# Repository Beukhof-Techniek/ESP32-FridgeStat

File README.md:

# ESP32-FridgeStat

ESP32 Refrigerator Thermostat with Signal K support
-----

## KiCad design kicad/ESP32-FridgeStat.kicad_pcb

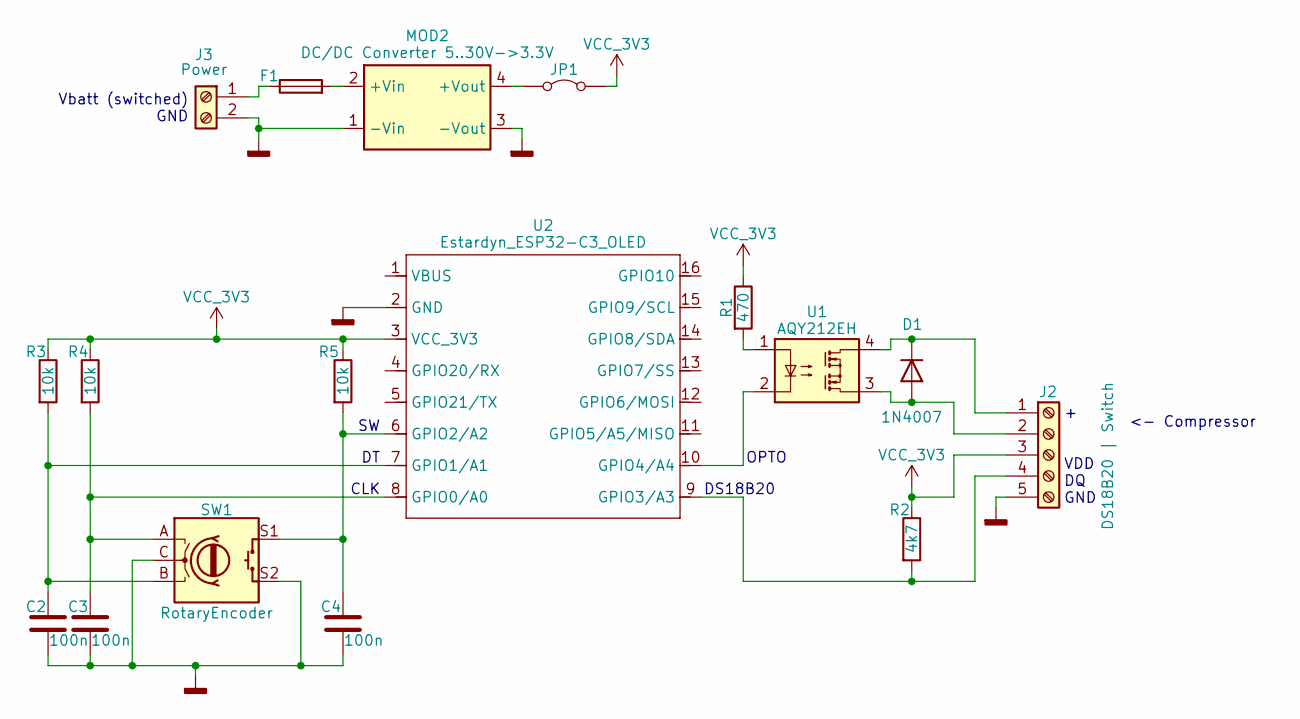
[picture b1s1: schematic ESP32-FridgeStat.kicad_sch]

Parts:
C2, C3, C4: 100n; C_Disc_D3.0mm_W1.6mm_P2.50mm
D1: 1N4007; D_DO-34_SOD68_P7.62mm_Horizontal
F1: 250mA F; Fuseholder_Littelfuse_Nano2_154x
J2: DS18B20 | Switch; TerminalBlock_MaiXu_MX126-5.0-05P_1x05_P5.00mm
J3: Power; TerminalBlock_MaiXu_MX126-5.0-02P_1x02_P5.00mm
JP1: Jumper_2_Bridged; TestPoint_2Pads_Pitch2.54mm_Drill0.8mm
MOD2: DC/DC Converter 5..30V->3.3V; DCDC_Converter_Aliexpress_4pin_17x12mm
R1: 470; R_Axial_DIN0204_L3.6mm_D1.6mm_P7.62mm_Horizontal
R2: 4k7; R_Axial_DIN0204_L3.6mm_D1.6mm_P7.62mm_Horizontal
R3, R4, R5: 10k; R_Axial_DIN0204_L3.6mm_D1.6mm_P7.62mm_Horizontal
SW1: RotaryEncoder; RotaryEncoder_Alps_EC11E-Switch_Vertical_H20mm
U1: AQY212EH; DIP-4_W7.62mm
U2: Estardyn_ESP32-C3_OLED; ESTARDYN-ESP32C3-OLED

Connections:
GNDD: C2.2, C3.2, C4.2, J2.5, J3.2, MOD2.1 (-Vin), MOD2.3 (-Vout), SW1.C, SW1.S2, U2.2 (GND)
unnamed: D1.2 (A), J2.2, U1.3
unnamed: D1.1 (K), J2.1, U1.4
unnamed: J2.4, R2.2, U2.9 (GPIO3/A3)
unnamed: F1.1, J3.1
unnamed: JP1.1 (A), MOD2.4 (+Vout)
unnamed: F1.2, MOD2.2 (+Vin)
unnamed: R1.2, U1.1
unnamed: C3.1, R4.2, SW1.A, U2.8 (GPIO0/A0)
unnamed: C2.1, R3.2, SW1.B, U2.7 (GPIO1/A1)
unnamed: C4.1, R5.2, SW1.S1, U2.6 (GPIO2/A2)
unnamed: U1.2, U2.10 (GPIO4/A4)
VCC_3V3: J2.3, JP1.2 (B), R1.1, R2.1, R3.1, R4.1, R5.1, U2.3 (VCC_3V3)

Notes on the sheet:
Vbatt (switched) GND
DS18B20
OPTO
<- Compressor
+ VDD DQ GND
CLK

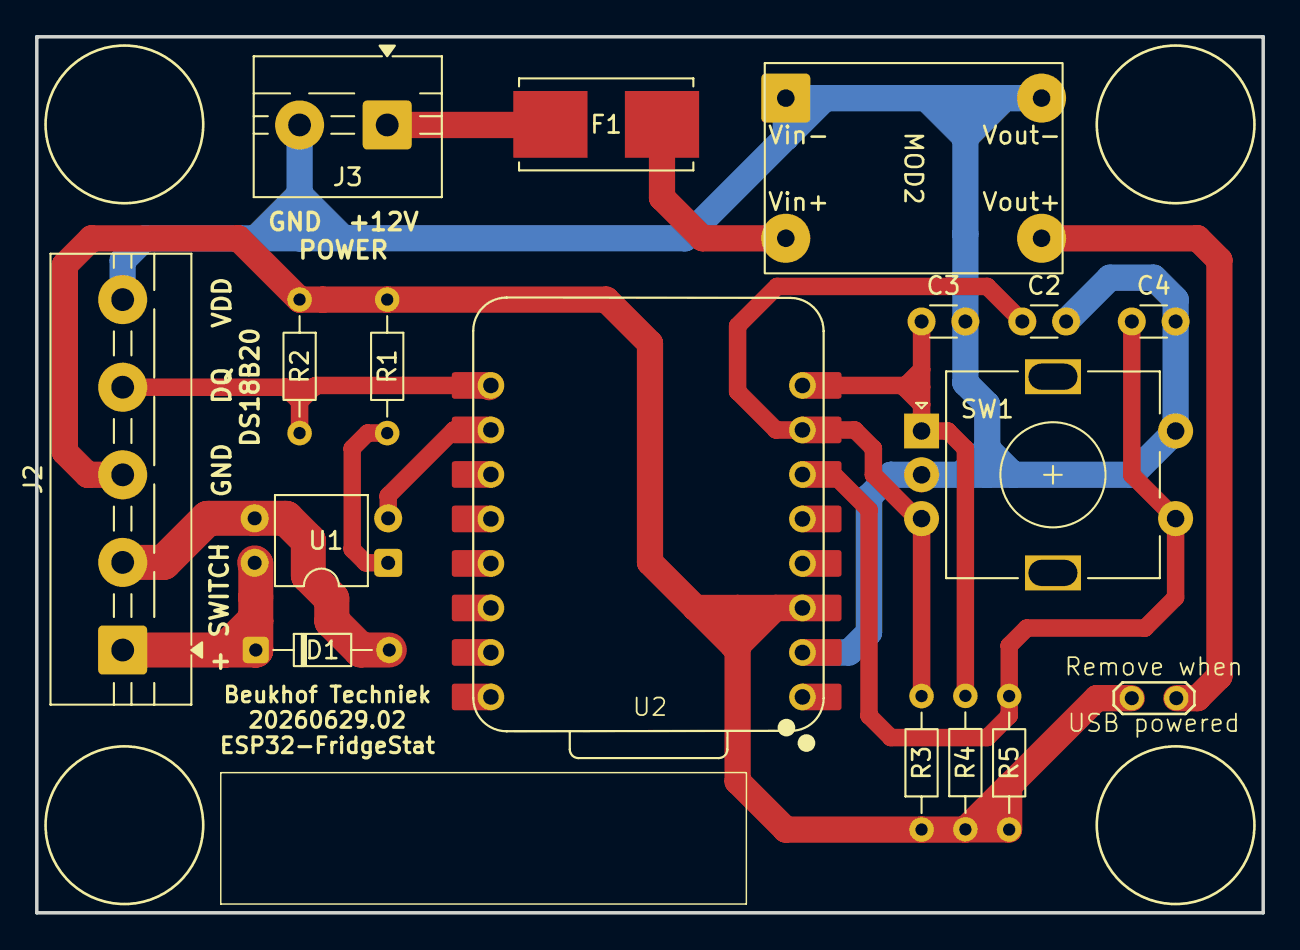
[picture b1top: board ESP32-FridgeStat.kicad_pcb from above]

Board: 2 copper layers, 70.0 x 50.0 mm, 17 parts (0 on the bottom side), 13 nets.
